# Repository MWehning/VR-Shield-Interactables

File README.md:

View full VR-Shield project at:
https://www.openhardware.io/view/33050

## Kicad files required to replicate the VR-Dapter for attaching sensors to the VR-Shield system. 
Tested with:
* MPU6050
* QMC5883L
* BH1750

# Required components:

*  1x 180 Ohm SMD-Resistor (0805)
* 1x LED Red (0805)
* 2x 02x03 angled pin header (2.54mm)
* 1x 01x08 vertical pin header (2.54mm)
* 2x 01x02 vertical pin header (2.00mm)
* 2x pin jumper for vertical pin header (2.00mm, for configuration of led and pin layout)

## Build instructions can be found at /bom/ibom.html

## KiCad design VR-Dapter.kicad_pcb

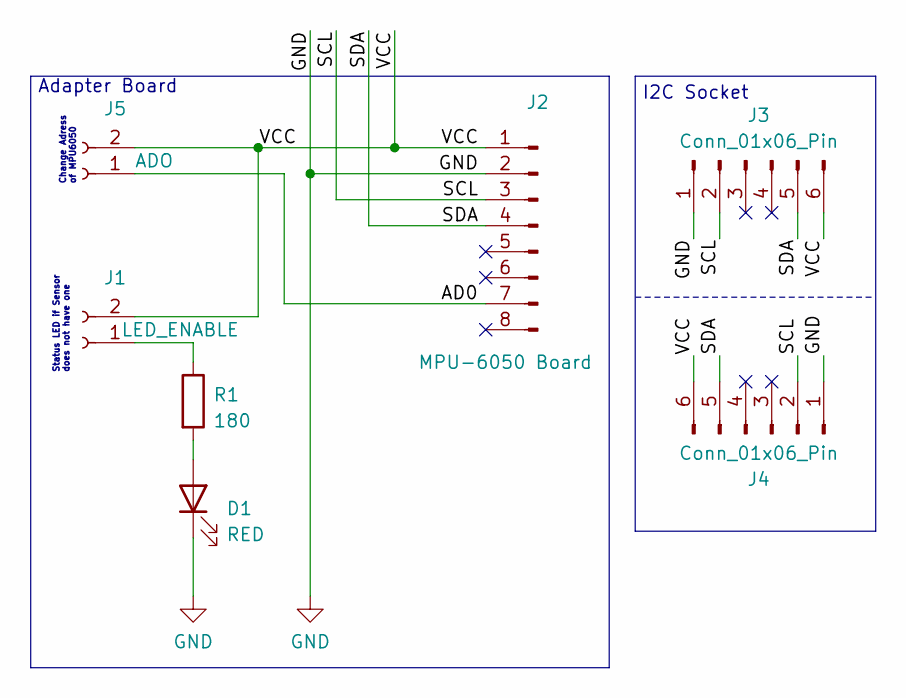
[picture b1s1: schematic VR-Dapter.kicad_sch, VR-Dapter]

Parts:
D1: RED; LED_0805_2012Metric_Pad1.15x1.40mm_HandSolder
J1: LED_ENABLE; PinSocket_1x02_P2.00mm_Vertical
J2: MPU-6050 Board; PinHeader_1x08_P2.54mm_Vertical
J3, J4: Conn_01x06_Pin; PinHeader_2x03_P2.54mm_Horizontal
J5: ADO; PinSocket_1x02_P2.00mm_Vertical
R1: 180; R_0805_2012Metric_Pad1.20x1.40mm_HandSolder

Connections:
/SCL: J2.3, J3.2, J4.2
/SDA: J2.4, J3.5, J4.5
/VCC: J1.2, J2.1, J3.6, J4.6, J5.2
GND: D1.1 (K), J2.2, J3.1, J4.1
unnamed: D1.2 (A), R1.2
unnamed: J1.1, R1.1
unnamed: J2.7, J5.1

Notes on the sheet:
Adapter Board
Status LED if Sensor does not have one
I2C Socket
Change Adress of MPU6050

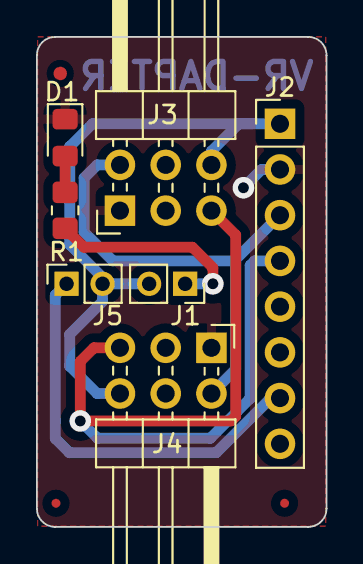
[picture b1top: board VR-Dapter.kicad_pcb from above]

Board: 2 copper layers, 16.1 x 27.2 mm, 10 parts (0 on the bottom side), 7 nets.

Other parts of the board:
FID**: Fiducial_0.5mm_Mask1.5mm
FID**#2: Fiducial_0.5mm_Mask1.5mm
FID**#3: Fiducial RT

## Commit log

2023-05-15 Create LICENSE
2023-05-15 VR-Dapter PCB
2023-05-15 Added BOM

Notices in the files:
VR-Dapter.kicad_pcb:
License: Apache 2.0
